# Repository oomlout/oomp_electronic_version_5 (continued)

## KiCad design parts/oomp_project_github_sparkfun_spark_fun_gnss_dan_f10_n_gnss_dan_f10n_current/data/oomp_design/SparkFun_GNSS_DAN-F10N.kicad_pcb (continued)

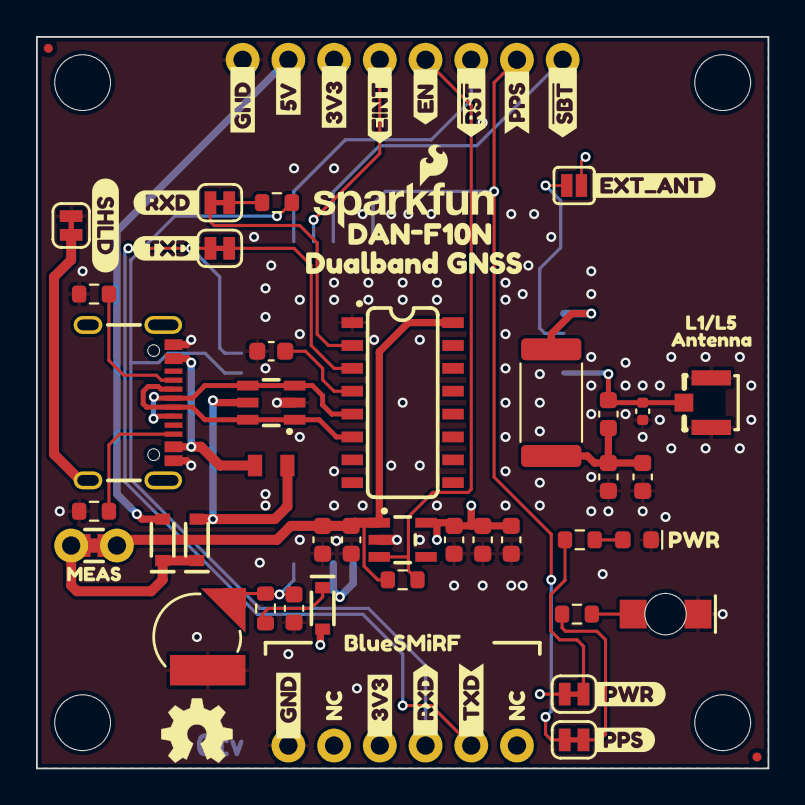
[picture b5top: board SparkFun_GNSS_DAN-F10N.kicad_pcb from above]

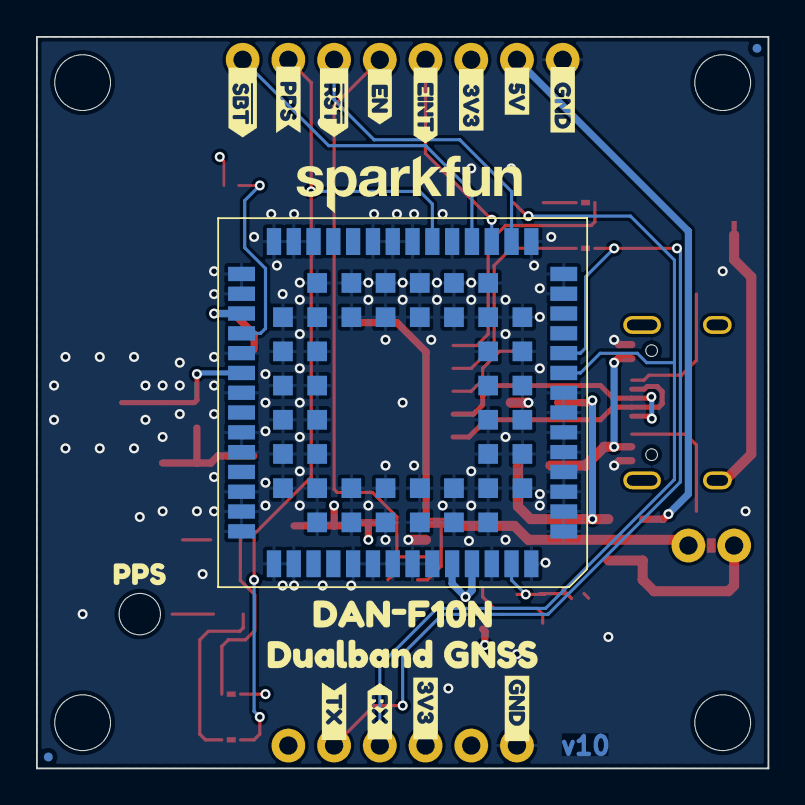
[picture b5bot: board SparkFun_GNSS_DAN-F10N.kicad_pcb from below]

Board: 4 copper layers, 40.6 x 40.6 mm, 93 parts (18 on the bottom side), 33 nets.

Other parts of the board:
Ref**: Val**; OSHW_Logo_4mm
kibuzzard-64C2E6A3: G***; kibuzzard-64C2E6A3
kibuzzard-64C3DF93: G***; kibuzzard-64C3DF93
kibuzzard-67C7D06A: G***; kibuzzard-67C7D06A
kibuzzard-67C7D061: G***; kibuzzard-67C7D061
kibuzzard-67C52A06: G***; kibuzzard-67C52A06
kibuzzard-67C52AED: G***; kibuzzard-67C52AED
kibuzzard-67C52B01: G***; kibuzzard-67C52B01
kibuzzard-67C52B1C: G***; kibuzzard-67C52B1C
kibuzzard-67C52C8F: G***; kibuzzard-67C52C8F
kibuzzard-67C52CCE: G***; kibuzzard-67C52CCE
kibuzzard-67C52D79: G***; kibuzzard-67C52D79
kibuzzard-67C52D85: G***; kibuzzard-67C52D85
kibuzzard-67C52DD7: G***; kibuzzard-67C52DD7
kibuzzard-67C52DE1: G***; kibuzzard-67C52DE1
kibuzzard-67C52F63: G***; kibuzzard-67C52F63
kibuzzard-67C524B9: G***; kibuzzard-67C524B9
kibuzzard-67C524C4: G***; kibuzzard-67C524C4
kibuzzard-67C526AF: G***; kibuzzard-67C526AF
kibuzzard-67C526C1: G***; kibuzzard-67C526C1
kibuzzard-67C526DE: G***; kibuzzard-67C526DE
kibuzzard-67C526ED: G***; kibuzzard-67C526ED
kibuzzard-67C526F3: G***; kibuzzard-67C526F3
kibuzzard-67C526FD: G***; kibuzzard-67C526FD
kibuzzard-67C527CA: G***; kibuzzard-67C527CA
kibuzzard-67C529FB: G***; kibuzzard-67C529FB
kibuzzard-67C5273C: G***; kibuzzard-67C5273C
kibuzzard-67C5274E: G***; kibuzzard-67C5274E
kibuzzard-67C5275D: G***; kibuzzard-67C5275D
kibuzzard-67C5279A: G***; kibuzzard-67C5279A
kibuzzard-67C52692: G***; kibuzzard-67C52692
kibuzzard-67C52701: G***; kibuzzard-67C52701
kibuzzard-67C52734: G***; kibuzzard-67C52734
kibuzzard-67C52738: G***; kibuzzard-67C52738
kibuzzard-67C52789: G***; kibuzzard-67C52789
kibuzzard-67D33FB6, kibuzzard-67D33FB6#2: G***; kibuzzard-67D33FB6
kibuzzard-67D358AB: G***; kibuzzard-67D358AB
kibuzzard-67D3586F: G***; kibuzzard-67D3586F
kibuzzard-67D3589A: G***; kibuzzard-67D3589A
kibuzzard-67D35894: G***; kibuzzard-67D35894
kibuzzard-67EB0CBA: G***; kibuzzard-67EB0CBA
kibuzzard-6501FDDA: G***; kibuzzard-6501FDDA

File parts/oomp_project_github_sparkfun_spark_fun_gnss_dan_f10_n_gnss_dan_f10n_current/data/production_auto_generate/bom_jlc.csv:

Comment,Designator,Footprint,LCSC Part #
0.1uF,"C1,C10,C14,C16",SparkFun-Capacitor:C_0603_1608Metric,C14663
1.0uF,"C7,C9",SparkFun-Capacitor:C_0603_1608Metric,C5673
100k,R12,SparkFun-Resistor:R_0603_1608Metric,C25803
10uF,C15,SparkFun-Capacitor:C_0603_1608Metric,C19702
13.3,R6,SparkFun-Resistor:R_2512_6332Metric,C6981998
1k,"R3,R7",SparkFun-Resistor:R_0603_1608Metric,C2907002
330,R5,SparkFun-Resistor:R_0603_1608Metric,C2933198
33nH,L1,SparkFun-Capacitor:C_0603_1608Metric,
33pF,C17,SparkFun-Capacitor:C_0603_1608Metric,C107047
4.7k,R4,SparkFun-Resistor:R_0603_1608Metric,C23162
47pF,C2,SparkFun-Capacitor:C_0603_1608Metric,C105622
5.1k,"R1,R2",SparkFun-Resistor:R_0603_1608Metric,C23186
6.8mm_ML414H,BT1,SparkFun-Battery:ML414H_IV01E,
6V/0.5A/1A,F1,SparkFun-Fuse:0805,
BAT60A,"D2,D3",SparkFun-Semiconductor-Standard:SOD-323,
CH340C,U4,SparkFun-Semiconductor-Standard:SO-16,C84681
Conn_01x06,J2,SparkFun-Connector:1x06,C37208
Conn_01x08,J5,SparkFun-Connector:1x08,C492421
DAN-F10N,U6,SparkFun-GNSS:u-blox_DAN-F10N,
DT1042-04SO,U1,SparkFun-Semiconductor-Standard:SOT23-6,C460064
EXT_ANT,JP1,SparkFun-Jumper:Jumper_2_NO,
Green,D6,SparkFun-LED:LED_1206_Bottom_Green,
Measure,JP11,SparkFun-Jumper:Jumper_2_PTH_SMD_Combo-NC,
PESD0402,D4,SparkFun-Capacitor:C_0402_1005Metric,C316059
PMEG4005EJ,D5,SparkFun-Semiconductor-Standard:SOD-323,
Red,D1,SparkFun-LED:LED_0603_1608Metric_Red,
RT9080-3.3,U3,SparkFun-Semiconductor-Standard:SOT23-5,
USB_C_Receptacle,J1,SparkFun-Connector:USB-C_16,C2765186
Val**,J4,SparkFun-Connector:U.FL,
~,"JP2,JP3,JP7,JP9,JP10",SparkFun-Jumper:Jumper_2_NC_Trace,

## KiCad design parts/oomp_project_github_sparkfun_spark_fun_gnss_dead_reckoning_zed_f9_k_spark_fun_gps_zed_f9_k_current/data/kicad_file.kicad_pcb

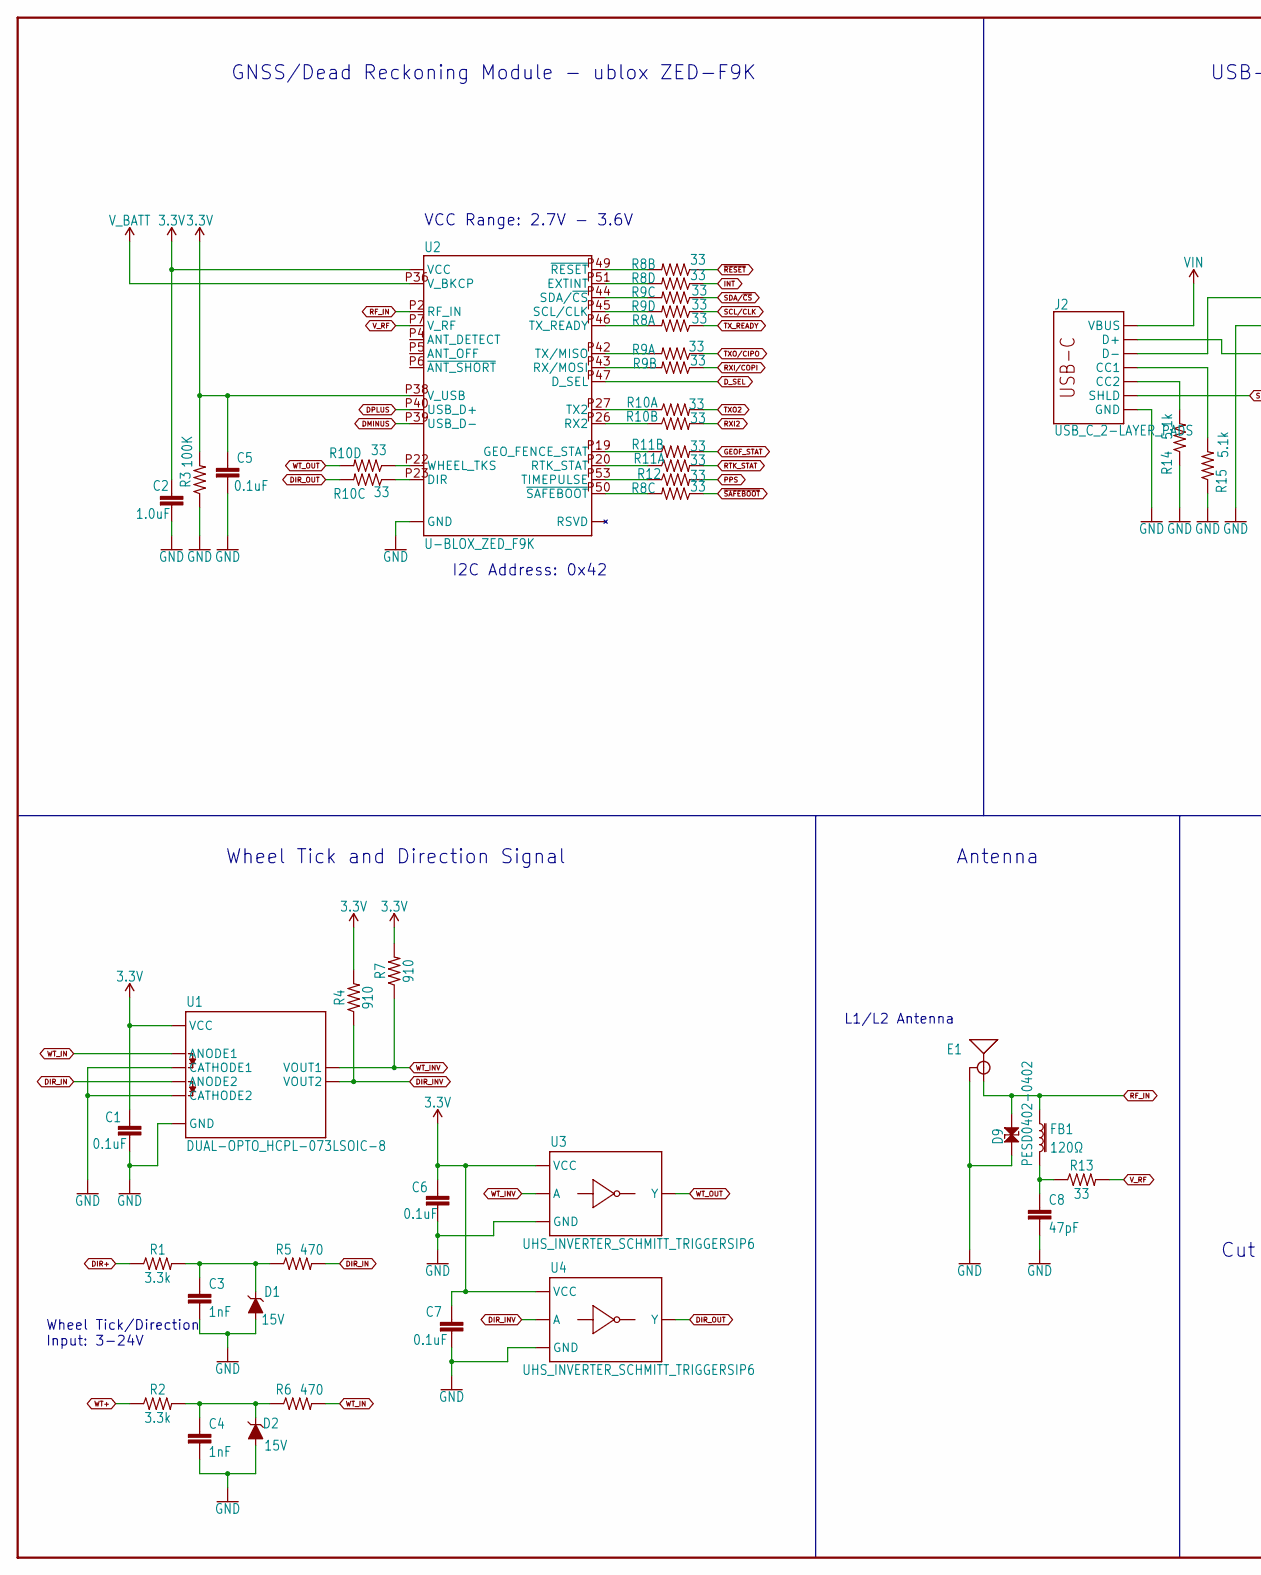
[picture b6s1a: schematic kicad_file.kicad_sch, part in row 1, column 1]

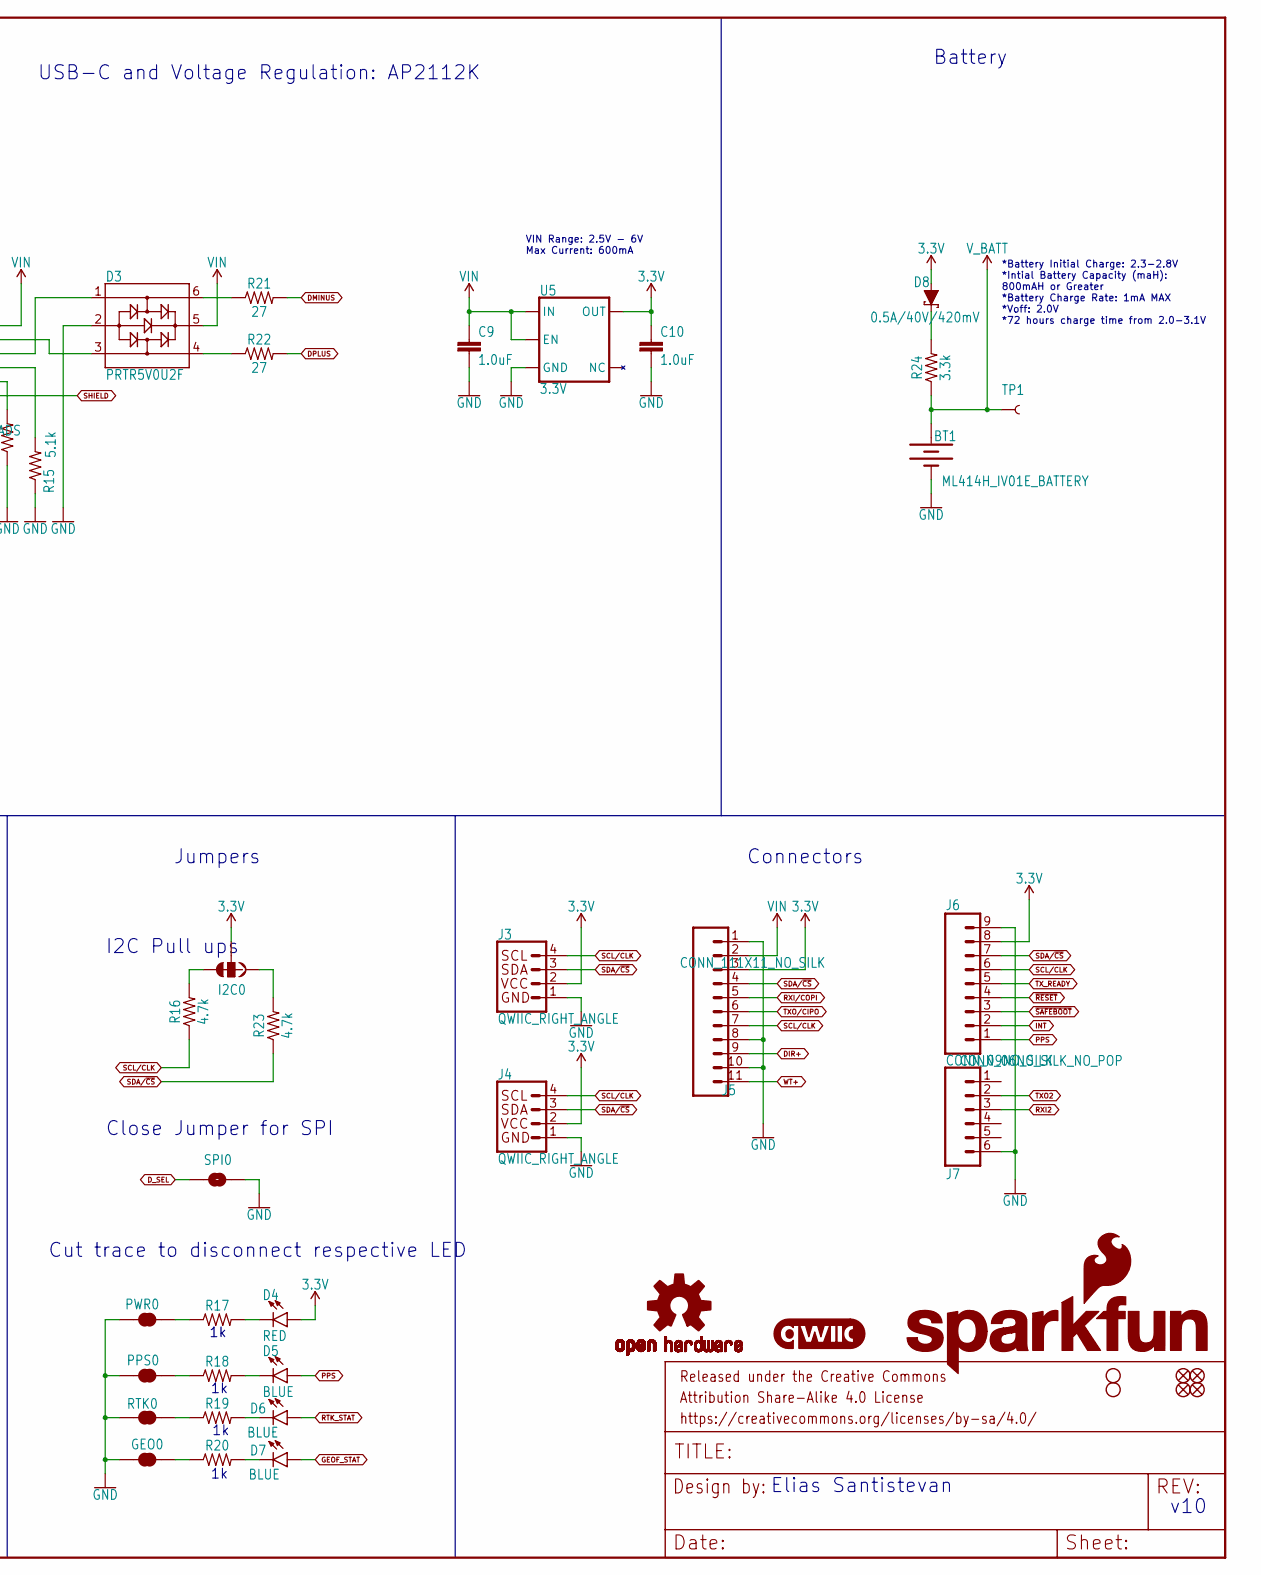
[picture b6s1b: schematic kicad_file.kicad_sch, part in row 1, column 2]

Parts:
$1_25_$_2020-03-30_22-52-05: STAND-OFFTIGHT; STAND-OFF-TIGHT
BT1: ML414H_IV01E_BATTERY; ML414H_IV01E
C1, C5, C6, C7: 0.1uF; 0402-TIGHT
C2, C9, C10: 1.0uF; 0402-TIGHT
C3, C4: 1nF; 0402
C8: 47pF; 0402
D1, D2: 15V; SOT23-3
D3: PRTR5V0U2F; SOT886
D4: RED; LED-0603
D5, D6, D7: BLUE; LED-0603
D8: 0.5A/40V/420mV; SOD-323
D9: PESD0402-0402; 0402; MOUSE_PART 650-PESD0402-140; DIGIKEY_PART PESD0402-140CT-ND
E1: ANTENNA-SMA-GROUNDEDEDGE_SMA; SMA-EDGE
FB1: 120Ω; 0402; MFG_PART BLM15HB121SN1D
FD1, FD2, FD3, FD4: FIDUCIALUFIDUCIAL; FIDUCIAL-MICRO
FRAME1: FRAME-LEDGER; CREATIVE_COMMONS
GEO0: JUMPER-SMT_2_NC_TRACE_SILK; SMT-JUMPER_2_NC_TRACE_SILK
H2: STAND-OFFTIGHT; STAND-OFF-TIGHT
I2C0: JUMPER-SMT_3_2-NC_TRACE_SILK; SMT-JUMPER_3_2-NC_TRACE_SILK
J2: USB_C_2-LAYER_PADS; USB-C-16P-2LAYER-PADS
J3, J4: QWIIC_RIGHT_ANGLE; JST04_1MM_RA
J5: CONN_111X11_NO_SILK; 1X11_NO_SILK
J6: CONN_09NO_SILK; 1X09_NO_SILK
J7: CONN_06NO_SILK_NO_POP; 1X06_NO_SILK
LOGO1: OSHW-LOGOS; OSHW-LOGO-S
LOGO2: QWIIC_LOGO_4MM; QWIIC_4MM
LOGO3: SFE_LOGO_NAME_FLAME.2_INCH; SFE_LOGO_NAME_FLAME_.2
PPS0: JUMPER-SMT_2_NC_TRACE_SILK; SMT-JUMPER_2_NC_TRACE_SILK
PWR0: JUMPER-SMT_2_NC_TRACE_SILK; SMT-JUMPER_2_NC_TRACE_SILK
R1, R2, R24: 3.3k; 0603
R3: 100K; 0402
R4, R7: 910; 0603
R5, R6: 470; 0603
R8, R9, R10, R11: 33; 1206_RA
R12, R13: 33; 0603
R14, R15: 5.1k; 0402
R16, R23: 4.7k; 0402-TIGHT
R17, R18, R19, R20: 1KOHM-0402-1/16W-1%; 0402
R21, R22: 27; 0603
RTK0: JUMPER-SMT_2_NC_TRACE_SILK; SMT-JUMPER_2_NC_TRACE_SILK
SPI0: JUMPER-SMT_2_NO_SILK; SMT-JUMPER_2_NO_SILK
TP1: TEST-POINT3X5; PAD.03X.05
U1: DUAL-OPTO_HCPL-073LSOIC-8; SO08
U2: U-BLOX_ZED_F9K; UBLOX_ZED_F9K
U3, U4: UHS_INVERTER_SCHMITT_TRIGGERSIP6; SIP6
U5: 3.3V; SOT23-5

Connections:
3.3V: C1.1, C2.1, C5.1, C6.1, C7.1, C10.1, D4.A, D8.A, I2C0.2, J3.2, J4.2, J5.3, J6.8, R3.2, R4.2, R7.2, U1.8 (VCC), U2.P33 (VCC), U2.P34 (VCC), U2.P38 (V_USB), U3.P6 (VCC), U4.P6 (VCC), U5.5 (OUT)
DIR+: J5.9, R1.1
DIR_IN: R5.2, U1.4 (ANODE2)
DIR_INV: R4.1, U1.6 (VOUT2), U4.P2 (A)
DIR_OUT: R10.P6 (2), U4.P4 (Y)
DMINUS: R21.2, U2.P39 (USB_D-)
DPLUS: R22.2, U2.P40 (USB_D+)
D_SEL: SPI0.1, U2.P47 (D_SEL)
GEOF_STAT: D7.A, R11.P7 (2)
GND: BT1.-, C1.2, C2.2, C3.2, C4.2, C5.2, C6.2, C7.2, C8.2, C9.2, C10.2, D1.1 (A), D2.1 (A), D3.2, D9.1, E1.GND@0 (GND), E1.GND@1 (GND), E1.GND@2 (GND), E1.GND@3 (GND), GEO0.1, J2.GND, J2.GND2 (GND), J3.1, J4.1, J5.1, J5.8, J5.10, J6.9, J7.6, PPS0.1, PWR0.1, R3.1, R14.1, R15.1, RTK0.1, SPI0.2, U1.2 (CATHODE1), U1.3 (CATHODE2), U1.5 (GND), U2.G1 (GND), U2.G2 (GND), U2.G3 (GND), U2.G4 (GND), U2.G5 (GND), U2.G6 (GND), U2.G7 (GND), U2.G8 (GND), U2.G9 (GND), U2.G10 (GND), U2.G11 (GND), U2.G12 (GND), U2.G13 (GND), U2.G14 (GND), U2.G15 (GND), U2.G16 (GND), U2.G17 (GND), U2.G18 (GND), U2.G19 (GND), U2.G20 (GND), U2.G21 (GND), U2.G22 (GND), U2.G23 (GND), U2.G24 (GND), U2.G25 (GND), U2.G26 (GND), U2.G27 (GND), U2.G28 (GND), U2.G29 (GND), U2.G30 (GND), U2.G31 (GND), U2.G32 (GND), U2.G33 (GND), U2.G34 (GND), U2.G35 (GND), U2.G36 (GND), U2.G37 (GND), U2.G38 (GND), U2.G39 (GND), U2.G40 (GND), U2.G41 (GND), U2.G42 (GND), U2.G43 (GND), U2.G44 (GND), U2.G45 (GND), U2.G46 (GND), U2.G47 (GND), U2.G48 (GND), U2.P1 (GND), U2.P3 (GND), U2.P12 (GND), U2.P14 (GND), U2.P32 (GND), U2.P37 (GND), U2.P41 (GND), U2.P48 (GND), U3.P3 (GND), U4.P3 (GND), U5.2 (GND)
INT: J6.2, R8.P4 (1)
unnamed: I2C0.1, R23.2
unnamed: D8.C, R24.2
unnamed: I2C0.3, R16.2
unnamed: D4.C, R17.2
unnamed: C8.1, FB1.2, R13.1
unnamed: D3.3, J2.A6 (D+), J2.B6 (D+)
unnamed: D3.1, J2.A7 (D-), J2.B7 (D-)
unnamed: PWR0.2, R17.1
unnamed: D3.6, R21.1
unnamed: D3.4, R22.1
unnamed: R8.P7 (2), U2.P49 (~RESET)
unnamed: R8.P5 (2), U2.P51 (EXTINT)
unnamed: J2.B5 (CC2), R14.2
unnamed: J2.A5 (CC1), R15.2
unnamed: R9.P6 (2), U2.P44 (SDA/~CS)
unnamed: R9.P5 (2), U2.P45 (SCL/CLK)
unnamed: R8.P8 (2), U2.P46 (TX_READY)
unnamed: R9.P8 (2), U2.P42 (TX/MISO)
unnamed: R9.P7 (2), U2.P43 (RX/MOSI)
unnamed: R10.P1 (1), U2.P27 (TX2)
unnamed: R19.1, RTK0.2
unnamed: PPS0.2, R18.1
unnamed: D5.C, R18.2
unnamed: D6.C, R19.2
unnamed: R10.P2 (1), U2.P26 (RX2)
unnamed: R11.P2 (1), U2.P19 (GEO_FENCE_STAT)
unnamed: R11.P1 (1), U2.P20 (RTK_STAT)
unnamed: R12.1, U2.P53 (TIMEPULSE)
unnamed: R8.P6 (2), U2.P50 (~SAFEBOOT)
unnamed: R10.P4 (1), U2.P22 (WHEEL_TKS)
unnamed: R10.P3 (1), U2.P23 (DIR)
unnamed: GEO0.2, R20.1
unnamed: D7.C, R20.2
unnamed: C4.1, D2.3 (C), R2.2, R6.1
unnamed: C3.1, D1.3 (C), R1.2, R5.1
PPS: D5.A, J6.1, R12.2
RF_IN: D9.2, E1.SIG (SIGNAL), FB1.1, U2.P2 (RF_IN)
RTK_STAT: D6.A, R11.P8 (2)
RXI2: J7.3, R10.P7 (2)
RXI/COPI: J5.5, R9.P2 (1)
SCL/CLK: J3.4, J4.4, J5.7, J6.6, R9.P4 (1), R16.1
SDA/~CS: J3.3, J4.3, J5.4, J6.7, R9.P3 (1), R23.1
SHIELD: J2.SHLD1 (SHLD), J2.SHLD2 (SHLD), J2.SHLD3 (SHLD), J2.SHLD4 (SHLD)
TXO2: J7.2, R10.P8 (2)
TXO/CIPO: J5.6, R9.P1 (1)
TX_READY: J6.5, R8.P1 (1)
VIN: C9.1, D3.5, J2.VBUS1 (VBUS), J2.VBUS2 (VBUS), J5.2, U5.1 (IN), U5.3 (EN)
V_BATT: BT1.+, R24.1, TP1.1, U2.P36 (V_BKCP)
V_RF: R13.2, U2.P7 (V_RF)
WT+: J5.11, R2.1
WT_IN: R6.2, U1.1 (ANODE1)
WT_INV: R7.1, U1.7 (VOUT1), U3.P2 (A)
WT_OUT: R10.P5 (2), U3.P4 (Y)
~RESET: J6.4, R8.P2 (1)
~SAFEBOOT: J6.3, R8.P3 (1)

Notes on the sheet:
Elias Santistevan
Wheel Tick and Direction Signal
Antenna
*Battery Initial Charge: 2.3-2.8V *Intial Battery Capacity (maH): 800mAH or Greater *Battery Charge Rate: 1mA MAX *Voff: 2.0V *72 hours charge time from 2.0-3.1V
Jumpers
v10
Battery
Close Jumper for SPI
Connectors
I2C Address: 0x42
I2C Pull ups
Cut trace to disconnect respective LED
USB-C and Voltage Regulation: AP2112K
GNSS/Dead Reckoning Module - ublox ZED-F9K
VIN Range: 2.5V - 6V Max Current: 600mA
VCC Range: 2.7V - 3.6V
L1/L2 Antenna
Wheel Tick/Direction Input: 3-24V

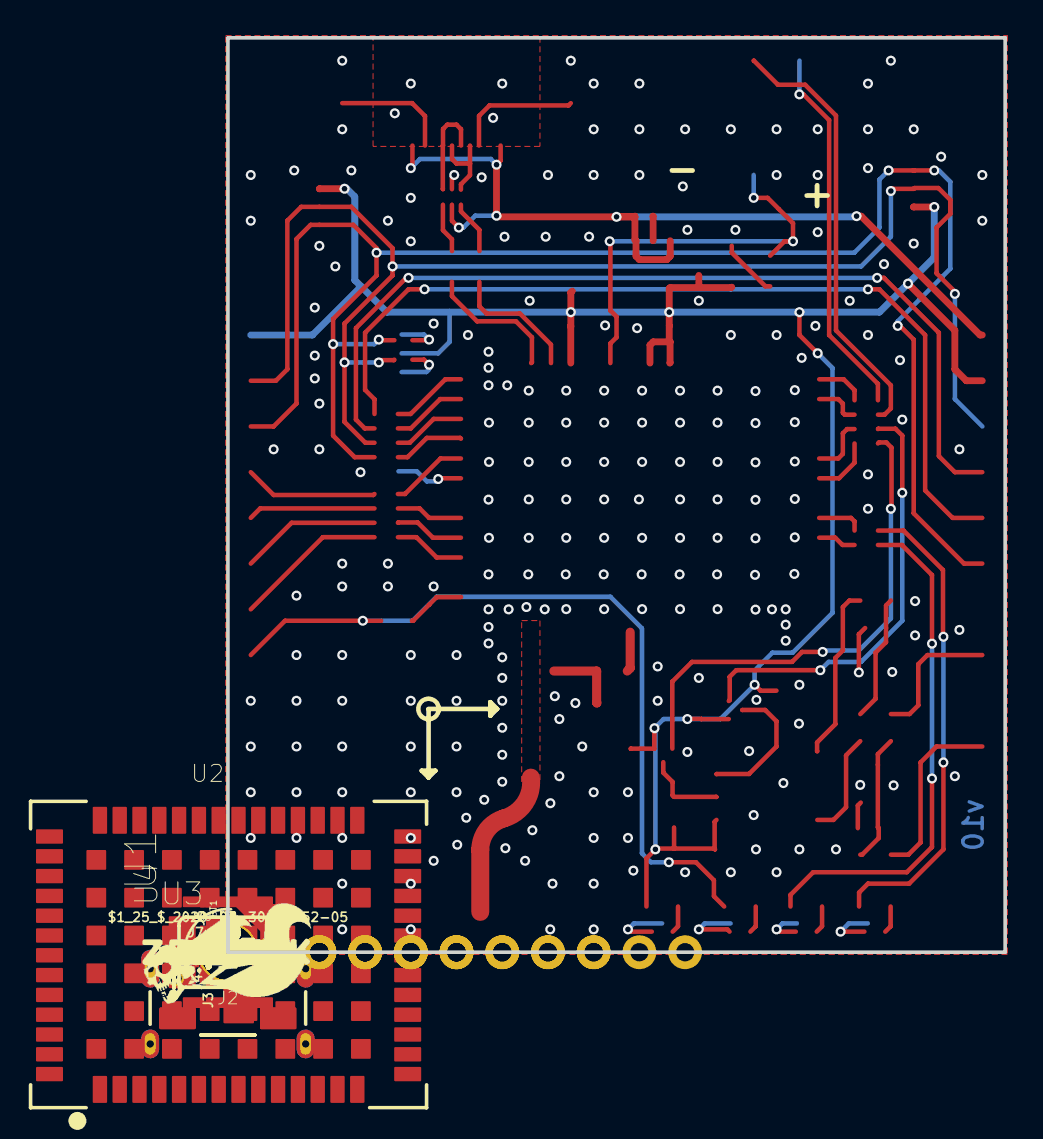
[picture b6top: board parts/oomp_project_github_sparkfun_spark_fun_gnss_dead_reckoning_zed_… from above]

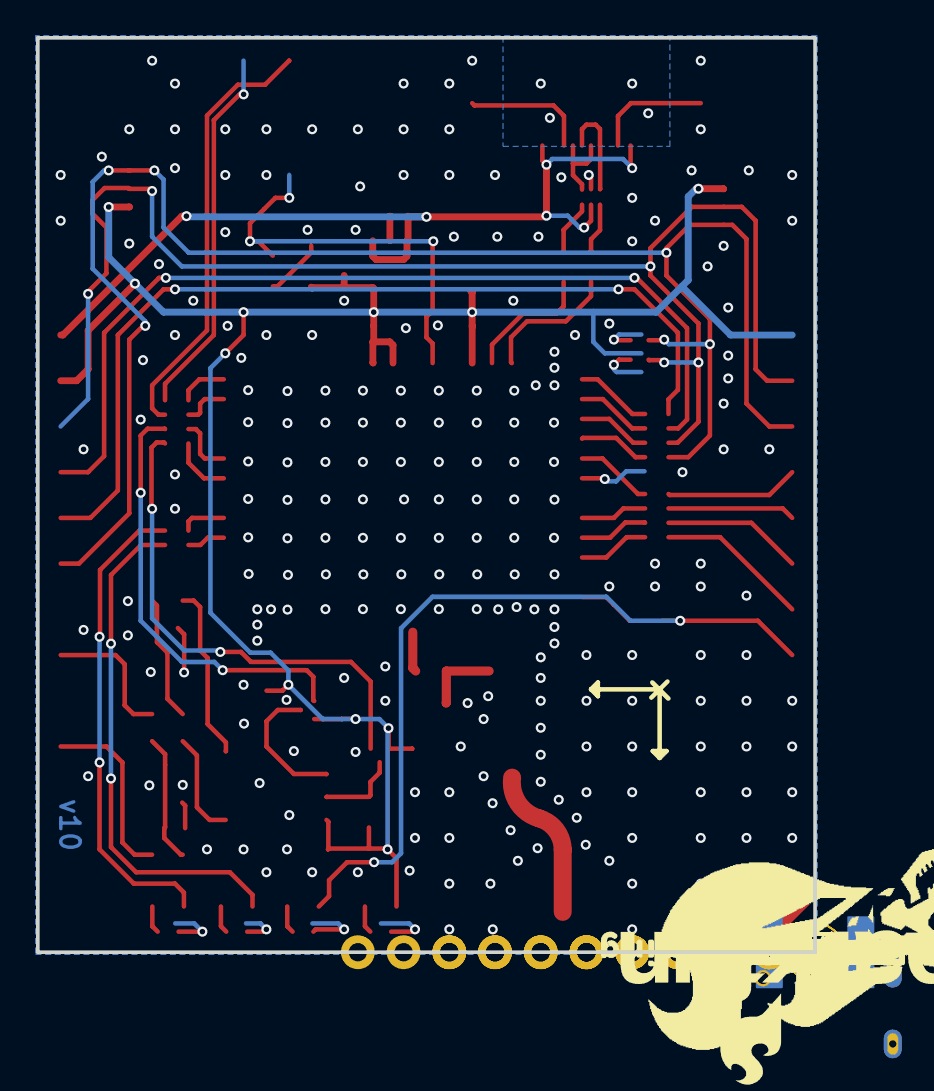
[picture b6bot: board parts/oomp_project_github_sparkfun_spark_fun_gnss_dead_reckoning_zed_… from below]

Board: 2 copper layers, 43.2 x 50.8 mm, 149 parts (47 on the bottom side), 66 nets.

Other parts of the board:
H1, H4: STAND-OFFTIGHT; STAND-OFF-TIGHT
U$1: PWR22
U$2: PPS21
U$3: GEO23
U$4: RTK24
U$5: #W##16
U$6: #W##15
U$7, U$14, U$22, U$37, U$55: #3V3#6
U$8: #D##13
U$9: #D##14
U$10: #SCK#12
U$11: #CIPO#10
U$12: #COPI#9
U$13: ##CS##11
U$15, U$24: #5V#1
U$16, U$17, U$25, U$36, U$44, U$58: #GND#0
U$18: #TXO2#20
U$19, U$20: DEAD#RECKONING#GPS#BOARD#SILK#FINAL#JPG
U$21: RX224
U$23: BLK225
U$26: GRN226
U$27: #SDA##CS##10
U$28: #RXI#COPI#8
U$30: #SCL#SCK#12
U$31: #D##6
U$32: X1
U$33: #D##7
U$34: #W##4
U$35: #W##5
U$38: #SDA#6
U$39: #SCL#7
U$40: #TXR#3
U$41: ##RST##16
U$42: ##SFBT##17
U$43: #INT#8
U$45: #PPS#0
U$46: #RTK#25
U$47: #GEO#24
U$48: #PPS#21
U$49: L1#L2229
U$50, U$52: Y2
U$51: #PWR#23
U$53: #SPI#22
U$54: #I2C#23
U$56: #SDA#12
U$57, U$63: Z0
U$59: #RXI2#227
U$60: #TXO2#1
U$61: BLK227
U$62: ANTENNA229
U$64: GRN228
U$65: GNSS#DEAD_RECKONING230
U$66: #SCL#13
U$67: #TXR#19
U$68: ##RST##17
U$69: ##SFBT##18
U$70: #INT#14
U$71: #PPS#20
U$72, U$73: ZED#F9K230
U$74: #TXO#CIPO#9
